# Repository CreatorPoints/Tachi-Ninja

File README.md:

# Tachi Ninja V2
A 60% Silent Linear mechanical keyboard that has per key RGB lighting and a display for pure asthetics! Made so that I can advance more in this fun cad pathway! [Now Hot-Swappable!]

---

## What was fun to make and what wasnt:
Well, it was overall a great project, I liked the most is the designing the pcb and making the case of this keyboard. But the ABSOLUTE brutal part was manually tracing all 424 pads :skull:

---

## Why did I make this?
I made it because I wanted a actually good keyboard, so instead of buying from online I decided to make my own. Advantages are I get to control how it would be and ofcource the flex :cool:

---

## Whats this "V2" Thingy?
So, when this project was submitted for forge, the reviewer returned the project for multiple reasons, one of it being incomplete PCBA, so, I improvised with something much better. The table would be the best:
|V1|V2|
|--|--|
|Permanent MX Switches|Kailh MX Hot Swappable sockets|
|Very crampy keycaps|Follows universal 19.05mm rule for keyboards|
|More compact, less polished|Kinda less compact, more polished|

## Need this? Here!
So, you need this same keyboard? NO PROBLEM! Its open-source!
1) Download this repo [assuming you know how to... just run git clone in your terminal]
2) Order the PCB - Preferebly from [JLCPCB](jlcpcb.com)
3) Gather the rest of the parts. Check [BOM](./BOM.md) 
4) Case files are in /CAD. Its upto you how to print [#Printing-Legion on slack].
5) Once your assembled PCB arrives, hand-solder the hot-swap sockets and OLED into the board (these are excluded from PCBA since they're through-hole/socketed). Press-fit switches into the hot-swap sockets and mount the PCB into the case and snap on keycaps.
6) Flash the firmware, hold both the BOOT and NRST button when turning on, it turns the stm32 to bootloader mode, drop the .h and json files on a STM32CubeProgrammer and Follow the steps there and then you are good to go!
7) Plug in via USB-C, confirm all 61 keys register, RGB lights up per-key, and the OLED display turns on! Yippe!

---

## Components used:
The following stuffs were used... Very hacky :)
- STM32F072C8Tx
- 1N4148 (x61)
- Kailh MX Hot Swappable Sockets (x61)
- SK6812MINI-E (x63)
- Resistors (x3)
- Capacitors (x6)
- Smol Switches (x2) - For boot & NRST purposes
- USB C 2.0 Receptable 16P
- AMS1117-3.3V
- 0.91 Inch I2C OLED Screen
- USBLC6-2SC6

---
## BOM

| Item | Link | Price | Shipping Cost |
| --- | --- | --- | --- |
| Switches (70x) | [HMX Taro Silent Linear](https://stackskb.com/store/hmx-taro-silent-linear-switch-pack-of-10/) | ₹2,625.00 / $27.39 | Free |
| Stabilizers | [Durock V2 Screw-in Stabilizers](https://stackskb.com/store/durock-clear-screw-in-stabilizers-v2/?attribute_combination=4%2B1+Set&attribute_spacebar-size=6.25U) | ₹1,595.00 / $16.65 | Free |
| Keycaps | [dagaladoo Shine Through Keycaps](https://www.amazon.in/gp/product/B0DJH6L159/ref=ox_sc_act_title_1?smid=A2BWJVKSWP7TR2) | ₹2,500.00 / $26.12 | $5.00 |
| Hot Swap Sockets (70x) | [Gateron Sockets](https://stackskb.com/store/gateron-hotswap-sockets/) | ₹610.00 / $6.37 | Free |
| Solder Wire | [Lead-free Solder](https://www.amazon.in/SCHOFIC-Solder-Sn99-Ag0-3-Cu0-7-Weight-0-22lb/dp/B078C7SMKY/ref=sr_1_10?sr=8-10) | ₹385.00 / $4.02 | Free |
| PCB & Top Assembly (2 boards) | [JLCPCB](https://jlcpcb.com) | $53.21 | Included |
| Loose SMD Parts (LEDs, Diodes, CC Resistors) | [LCSC](https://www.lcsc.com) | $9.03 *(parts + handling)* | $42.03 |

Subtotal: $189.82  
Estimated Import Customs (20% – 45% on JLCPCB + LCSC):** ~$21.00 – $47.00 (~$36.50 mid)  
Total Estimated Request: ~$226.30

### For the full itemized breakdown, footprints, and part numbers, check:
[BOM.md](BOM.md)

---

## Images!

### Wait, its V1

### From here V2 Development begins

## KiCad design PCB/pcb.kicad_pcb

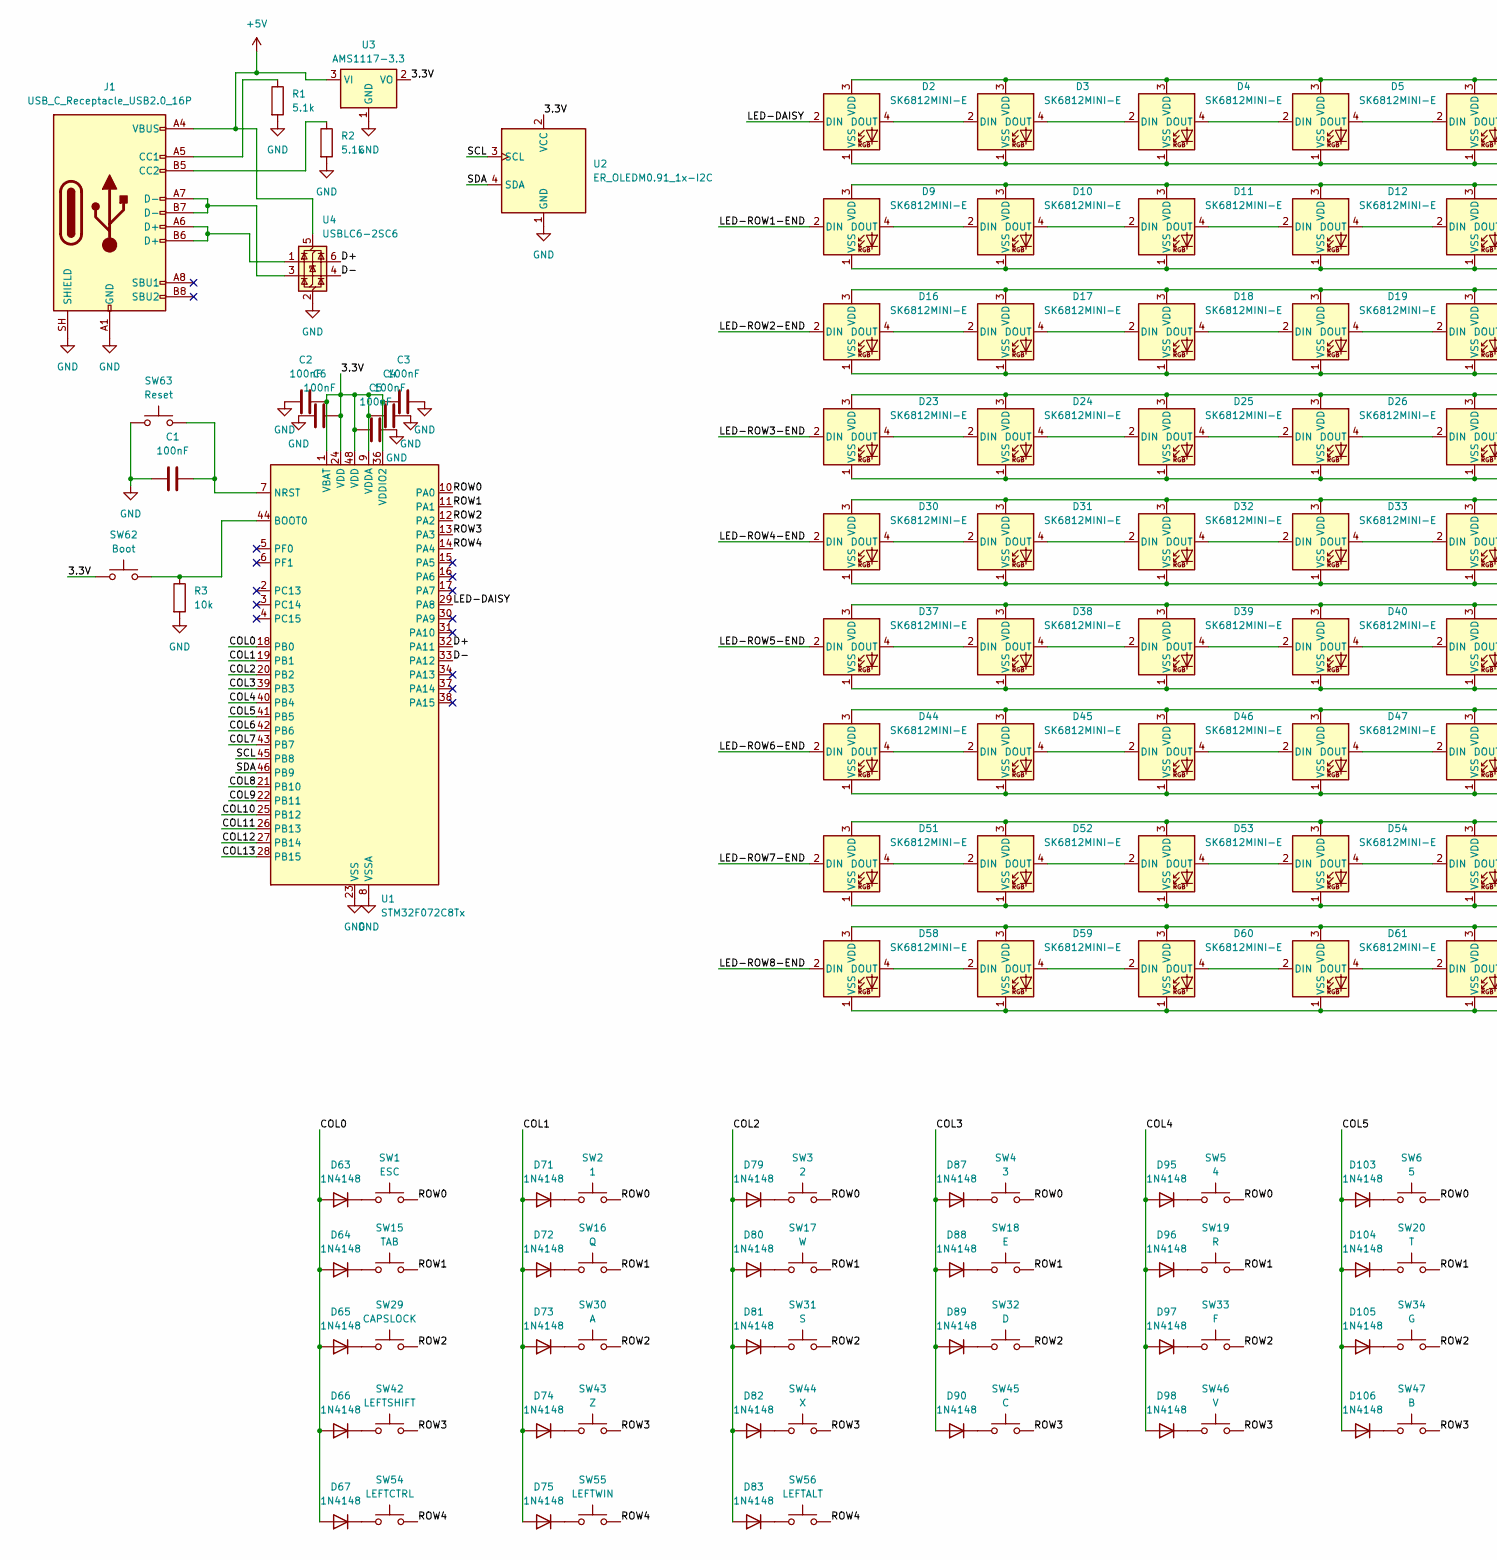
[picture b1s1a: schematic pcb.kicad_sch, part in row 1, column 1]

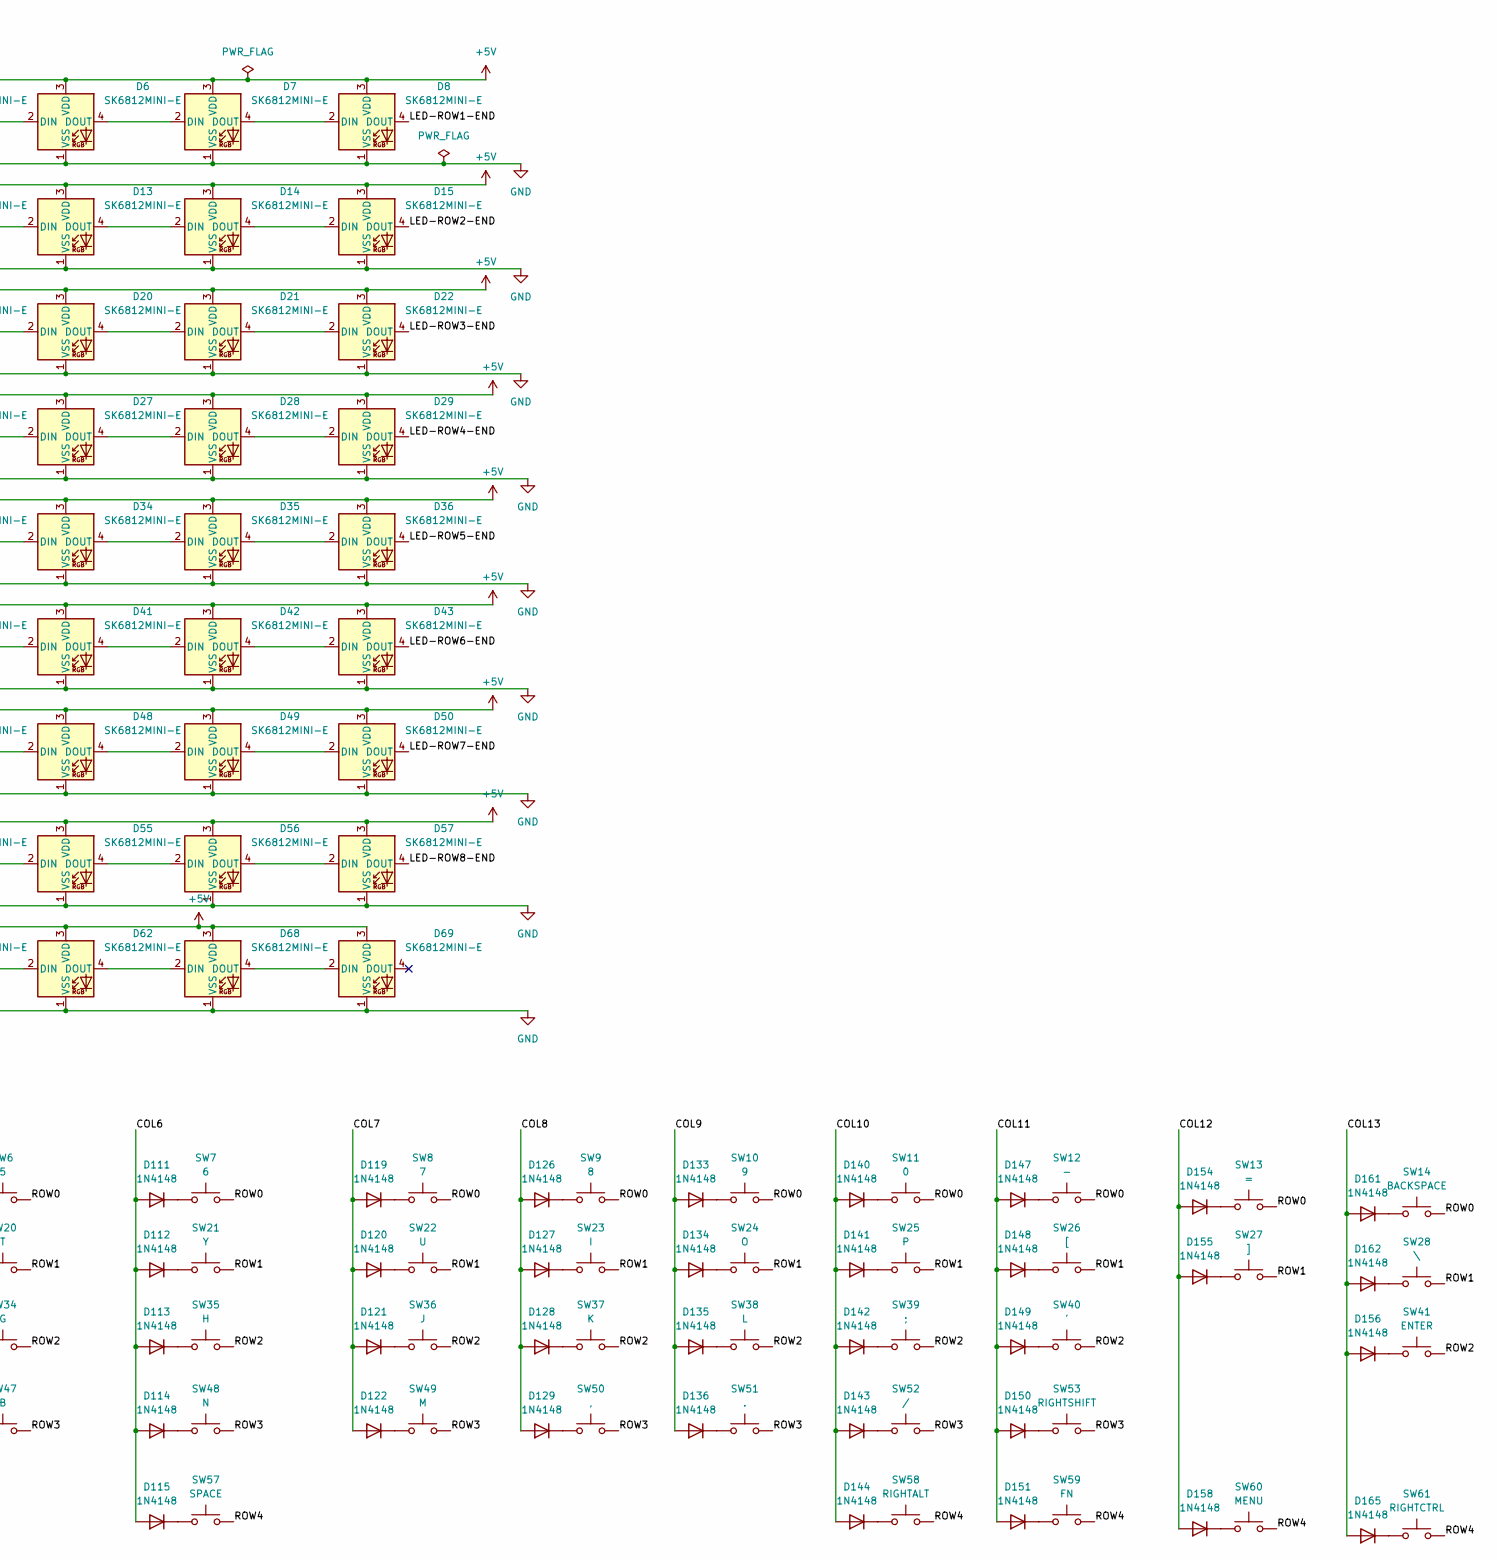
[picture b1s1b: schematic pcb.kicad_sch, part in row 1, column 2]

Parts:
C1, C2, C3, C4, C5, C6: 100nF; C_0805_2012Metric
D2, D3, D4, D5, D6, D7, D8, D9, D10, D11, D12, D13, D14, D15, D16, D17, D18, D19, D20, D21, D22, D23, D24, D25, D26, D27, D28, D29, D30, D31, D32, D33, D34, D35, D36, D37, D38, D39, D40, D41, D42, D43, D44, D45, D46, D47, D48, D49, D50, D51, D52, D53, D54, D55, D56, D57, D58, D59, D60, D61, D62, D68, D69: SK6812MINI-E; LED_SK6812MINI-E_3.2x2.8mm_P1.5mm_ReverseMount
D63, D64, D65, D66, D67, D71, D72, D73, D74, D75, D79, D80, D81, D82, D83, D87, D88, D89, D90, D95, D96, D97, D98, D103, D104, D105, D106, D111, D112, D113, D114, D115, D119, D120, D121, D122, D126, D127, D128, D129, D133, D134, D135, D136, D140, D141, D142, D143, D144, D147, D148, D149, D150, D151, D154, D155, D156, D158, D161, D162, D165: 1N4148; D_DO-35_SOD27_P7.62mm_Horizontal
J1: USB_C_Receptacle_USB2.0_16P; USB_C_Receptacle_HCTL_HC-TYPE-C-16P-01A
R1, R2: 5.1k; R_0603_1608Metric
R3: 10k; R_0603_1608Metric
SW1: ESC; SW_Hotswap_Kailh_MX_1.00u
SW2: 1; SW_Hotswap_Kailh_MX_1.00u
SW3: 2; SW_Hotswap_Kailh_MX_1.00u
SW4: 3; SW_Hotswap_Kailh_MX_1.00u
SW5: 4; SW_Hotswap_Kailh_MX_1.00u
SW6: 5; SW_Hotswap_Kailh_MX_1.00u
SW7: 6; SW_Hotswap_Kailh_MX_1.00u
SW8: 7; SW_Hotswap_Kailh_MX_1.00u
SW9: 8; SW_Hotswap_Kailh_MX_1.00u
SW10: 9; SW_Hotswap_Kailh_MX_1.00u
SW11: 0; SW_Hotswap_Kailh_MX_1.00u
SW12: -; SW_Hotswap_Kailh_MX_1.00u
SW13: =; SW_Hotswap_Kailh_MX_1.00u
SW14: BACKSPACE; SW_Hotswap_Kailh_MX_2.00u
SW15: TAB; SW_Hotswap_Kailh_MX_1.50u
SW16: Q; SW_Hotswap_Kailh_MX_1.00u
SW17: W; SW_Hotswap_Kailh_MX_1.00u
SW18: E; SW_Hotswap_Kailh_MX_1.00u
SW19: R; SW_Hotswap_Kailh_MX_1.00u
SW20: T; SW_Hotswap_Kailh_MX_1.00u
SW21: Y; SW_Hotswap_Kailh_MX_1.00u
SW22: U; SW_Hotswap_Kailh_MX_1.00u
SW23: I; SW_Hotswap_Kailh_MX_1.00u
SW24: O; SW_Hotswap_Kailh_MX_1.00u
SW25: P; SW_Hotswap_Kailh_MX_1.00u
SW26: [; SW_Hotswap_Kailh_MX_1.00u
SW27: ]; SW_Hotswap_Kailh_MX_1.00u
SW28: \; SW_Hotswap_Kailh_MX_1.50u
SW29: CAPSLOCK; SW_Hotswap_Kailh_MX_1.75u
SW30: A; SW_Hotswap_Kailh_MX_1.00u
SW31: S; SW_Hotswap_Kailh_MX_1.00u
SW32: D; SW_Hotswap_Kailh_MX_1.00u
SW33: F; SW_Hotswap_Kailh_MX_1.00u
SW34: G; SW_Hotswap_Kailh_MX_1.00u
SW35: H; SW_Hotswap_Kailh_MX_1.00u
SW36: J; SW_Hotswap_Kailh_MX_1.00u
SW37: K; SW_Hotswap_Kailh_MX_1.00u
SW38: L; SW_Hotswap_Kailh_MX_1.00u
SW39: ;; SW_Hotswap_Kailh_MX_1.00u
SW40: '; SW_Hotswap_Kailh_MX_1.00u
SW41: ENTER; SW_Hotswap_Kailh_MX_2.25u
SW42: LEFTSHIFT; SW_Hotswap_Kailh_MX_2.25u
SW43: Z; SW_Hotswap_Kailh_MX_1.00u
SW44: X; SW_Hotswap_Kailh_MX_1.00u
SW45: C; SW_Hotswap_Kailh_MX_1.00u
SW46: V; SW_Hotswap_Kailh_MX_1.00u
SW47: B; SW_Hotswap_Kailh_MX_1.00u
SW48: N; SW_Hotswap_Kailh_MX_1.00u
SW49: M; SW_Hotswap_Kailh_MX_1.00u
SW50: ,; SW_Hotswap_Kailh_MX_1.00u
SW51: .; SW_Hotswap_Kailh_MX_1.00u
SW52: /; SW_Hotswap_Kailh_MX_1.00u
SW53: RIGHTSHIFT; SW_Hotswap_Kailh_MX_2.75u
SW54: LEFTCTRL; SW_Hotswap_Kailh_MX_1.25u
SW55: LEFTWIN; SW_Hotswap_Kailh_MX_1.25u
SW56: LEFTALT; SW_Hotswap_Kailh_MX_1.25u
SW57: SPACE; SW_Hotswap_Kailh_MX_6.25u
SW58: RIGHTALT; SW_Hotswap_Kailh_MX_1.25u
SW59: FN; SW_Hotswap_Kailh_MX_1.25u
SW60: MENU; SW_Hotswap_Kailh_MX_1.25u
SW61: RIGHTCTRL; SW_Hotswap_Kailh_MX_1.25u
SW62: Boot; SW_SPST_B3U-1000P
SW63: Reset; SW_SPST_B3U-1000P
U1: STM32F072C8Tx; LQFP-48_7x7mm_P0.5mm
U2: ER_OLEDM0.91_1x-I2C
U3: AMS1117-3.3; SOT-223-3_TabPin2
U4: USBLC6-2SC6; SOT-23-6

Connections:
+5V: D2.3 (VDD), D3.3 (VDD), D4.3 (VDD), D5.3 (VDD), D6.3 (VDD), D7.3 (VDD), D8.3 (VDD), D9.3 (VDD), D10.3 (VDD), D11.3 (VDD), D12.3 (VDD), D13.3 (VDD), D14.3 (VDD), D15.3 (VDD), D16.3 (VDD), D17.3 (VDD), D18.3 (VDD), D19.3 (VDD), D20.3 (VDD), D21.3 (VDD), D22.3 (VDD), D23.3 (VDD), D24.3 (VDD), D25.3 (VDD), D26.3 (VDD), D27.3 (VDD), D28.3 (VDD), D29.3 (VDD), D30.3 (VDD), D31.3 (VDD), D32.3 (VDD), D33.3 (VDD), D34.3 (VDD), D35.3 (VDD), D36.3 (VDD), D37.3 (VDD), D38.3 (VDD), D39.3 (VDD), D40.3 (VDD), D41.3 (VDD), D42.3 (VDD), D43.3 (VDD), D44.3 (VDD), D45.3 (VDD), D46.3 (VDD), D47.3 (VDD), D48.3 (VDD), D49.3 (VDD), D50.3 (VDD), D51.3 (VDD), D52.3 (VDD), D53.3 (VDD), D54.3 (VDD), D55.3 (VDD), D56.3 (VDD), D57.3 (VDD), D58.3 (VDD), D59.3 (VDD), D60.3 (VDD), D61.3 (VDD), D62.3 (VDD), D68.3 (VDD), D69.3 (VDD), J1.A4 (VBUS), J1.A9 (VBUS), J1.B4 (VBUS), J1.B9 (VBUS), U3.3 (VI), U4.5 (VBUS)
/3.3V: C2.1, C3.2, C4.2, C5.2, C6.1, SW62.1, U1.1 (VBAT), U1.9 (VDDA), U1.24 (VDD), U1.36 (VDDIO2), U1.48 (VDD), U2.2 (VCC), U3.2 (VO)
/COL0: D63.2 (A), D64.2 (A), D65.2 (A), D66.2 (A), D67.2 (A), U1.18 (PB0)
/COL1: D71.2 (A), D72.2 (A), D73.2 (A), D74.2 (A), D75.2 (A), U1.19 (PB1)
/COL2: D79.2 (A), D80.2 (A), D81.2 (A), D82.2 (A), D83.2 (A), U1.20 (PB2)
/COL3: D87.2 (A), D88.2 (A), D89.2 (A), D90.2 (A), U1.39 (PB3)
/COL4: D95.2 (A), D96.2 (A), D97.2 (A), D98.2 (A), U1.40 (PB4)
/COL5: D103.2 (A), D104.2 (A), D105.2 (A), D106.2 (A), U1.41 (PB5)
/COL6: D111.2 (A), D112.2 (A), D113.2 (A), D114.2 (A), D115.2 (A), U1.42 (PB6)
/COL7: D119.2 (A), D120.2 (A), D121.2 (A), D122.2 (A), U1.43 (PB7)
/COL8: D126.2 (A), D127.2 (A), D128.2 (A), D129.2 (A), U1.21 (PB10)
/COL9: D133.2 (A), D134.2 (A), D135.2 (A), D136.2 (A), U1.22 (PB11)
/COL10: D140.2 (A), D141.2 (A), D142.2 (A), D143.2 (A), D144.2 (A), U1.25 (PB12)
/COL11: D147.2 (A), D148.2 (A), D149.2 (A), D150.2 (A), D151.2 (A), U1.26 (PB13)
/COL12: D154.2 (A), D155.2 (A), D158.2 (A), U1.27 (PB14)
/COL13: D156.2 (A), D161.2 (A), D162.2 (A), D165.2 (A), U1.28 (PB15)
/D+: U1.32 (PA11), U4.6 (I/O1)
/D-: U1.33 (PA12), U4.4 (I/O2)
/LED-DAISY: D2.2 (DIN), U1.29 (PA8)
/LED-ROW1-END: D8.4 (DOUT), D9.2 (DIN)
/LED-ROW2-END: D15.4 (DOUT), D16.2 (DIN)
/LED-ROW3-END: D22.4 (DOUT), D23.2 (DIN)
/LED-ROW4-END: D29.4 (DOUT), D30.2 (DIN)
/LED-ROW5-END: D36.4 (DOUT), D37.2 (DIN)
/LED-ROW6-END: D43.4 (DOUT), D44.2 (DIN)
/LED-ROW7-END: D50.4 (DOUT), D51.2 (DIN)
/LED-ROW8-END: D57.4 (DOUT), D58.2 (DIN)
/ROW0: SW1.2, SW2.2, SW3.2, SW4.2, SW5.2, SW6.2, SW7.2, SW8.2, SW9.2, SW10.2, SW11.2, SW12.2, SW13.2, SW14.2, U1.10 (PA0)
/ROW1: SW15.2, SW16.2, SW17.2, SW18.2, SW19.2, SW20.2, SW21.2, SW22.2, SW23.2, SW24.2, SW25.2, SW26.2, SW27.2, SW28.2, U1.11 (PA1)
/ROW2: SW29.2, SW30.2, SW31.2, SW32.2, SW33.2, SW34.2, SW35.2, SW36.2, SW37.2, SW38.2, SW39.2, SW40.2, SW41.2, U1.12 (PA2)
/ROW3: SW42.2, SW43.2, SW44.2, SW45.2, SW46.2, SW47.2, SW48.2, SW49.2, SW50.2, SW51.2, SW52.2, SW53.2, U1.13 (PA3)
/ROW4: SW54.2, SW55.2, SW56.2, SW57.2, SW58.2, SW59.2, SW60.2, SW61.2, U1.14 (PA4)
/SCL: U1.45 (PB8), U2.3 (SCL)
/SDA: U1.46 (PB9), U2.4 (SDA)
GND: C1.1, C2.2, C3.1, C4.1, C5.1, C6.2, D2.1 (VSS), D3.1 (VSS), D4.1 (VSS), D5.1 (VSS), D6.1 (VSS), D7.1 (VSS), D8.1 (VSS), D9.1 (VSS), D10.1 (VSS), D11.1 (VSS), D12.1 (VSS), D13.1 (VSS), D14.1 (VSS), D15.1 (VSS), D16.1 (VSS), D17.1 (VSS), D18.1 (VSS), D19.1 (VSS), D20.1 (VSS), D21.1 (VSS), D22.1 (VSS), D23.1 (VSS), D24.1 (VSS), D25.1 (VSS), D26.1 (VSS), D27.1 (VSS), D28.1 (VSS), D29.1 (VSS), D30.1 (VSS), D31.1 (VSS), D32.1 (VSS), D33.1 (VSS), D34.1 (VSS), D35.1 (VSS), D36.1 (VSS), D37.1 (VSS), D38.1 (VSS), D39.1 (VSS), D40.1 (VSS), D41.1 (VSS), D42.1 (VSS), D43.1 (VSS), D44.1 (VSS), D45.1 (VSS), D46.1 (VSS), D47.1 (VSS), D48.1 (VSS), D49.1 (VSS), D50.1 (VSS), D51.1 (VSS), D52.1 (VSS), D53.1 (VSS), D54.1 (VSS), D55.1 (VSS), D56.1 (VSS), D57.1 (VSS), D58.1 (VSS), D59.1 (VSS), D60.1 (VSS), D61.1 (VSS), D62.1 (VSS), D68.1 (VSS), D69.1 (VSS), J1.A1 (GND), J1.A12 (GND), J1.B1 (GND), J1.B12 (GND), J1.SH (SHIELD), R1.2, R2.2, R3.2, SW63.1, U1.8 (VSSA), U1.23 (VSS), U1.35 (VSS), U1.47 (VSS), U2.1 (GND), U3.1 (GND), U4.2 (GND)
unnamed: D2.4 (DOUT), D3.2 (DIN)
unnamed: D3.4 (DOUT), D4.2 (DIN)
unnamed: D4.4 (DOUT), D5.2 (DIN)
unnamed: D5.4 (DOUT), D6.2 (DIN)
unnamed: D6.4 (DOUT), D7.2 (DIN)
unnamed: D7.4 (DOUT), D8.2 (DIN)
unnamed: D9.4 (DOUT), D10.2 (DIN)
unnamed: D10.4 (DOUT), D11.2 (DIN)
unnamed: D11.4 (DOUT), D12.2 (DIN)
unnamed: D12.4 (DOUT), D13.2 (DIN)
unnamed: D13.4 (DOUT), D14.2 (DIN)
unnamed: D14.4 (DOUT), D15.2 (DIN)
unnamed: D16.4 (DOUT), D17.2 (DIN)
unnamed: D17.4 (DOUT), D18.2 (DIN)
unnamed: D18.4 (DOUT), D19.2 (DIN)
unnamed: D19.4 (DOUT), D20.2 (DIN)
unnamed: D20.4 (DOUT), D21.2 (DIN)
unnamed: D21.4 (DOUT), D22.2 (DIN)
unnamed: D23.4 (DOUT), D24.2 (DIN)
unnamed: D24.4 (DOUT), D25.2 (DIN)
unnamed: D25.4 (DOUT), D26.2 (DIN)
unnamed: D26.4 (DOUT), D27.2 (DIN)
unnamed: D27.4 (DOUT), D28.2 (DIN)
unnamed: D28.4 (DOUT), D29.2 (DIN)
unnamed: D30.4 (DOUT), D31.2 (DIN)
unnamed: D31.4 (DOUT), D32.2 (DIN)
unnamed: D32.4 (DOUT), D33.2 (DIN)
unnamed: D33.4 (DOUT), D34.2 (DIN)
unnamed: D34.4 (DOUT), D35.2 (DIN)
unnamed: D35.4 (DOUT), D36.2 (DIN)
unnamed: D37.4 (DOUT), D38.2 (DIN)
unnamed: D38.4 (DOUT), D39.2 (DIN)
unnamed: D39.4 (DOUT), D40.2 (DIN)
unnamed: D40.4 (DOUT), D41.2 (DIN)
unnamed: D41.4 (DOUT), D42.2 (DIN)
unnamed: D42.4 (DOUT), D43.2 (DIN)
unnamed: D44.4 (DOUT), D45.2 (DIN)
unnamed: D45.4 (DOUT), D46.2 (DIN)
unnamed: D46.4 (DOUT), D47.2 (DIN)
unnamed: D47.4 (DOUT), D48.2 (DIN)
unnamed: D48.4 (DOUT), D49.2 (DIN)
unnamed: D49.4 (DOUT), D50.2 (DIN)
unnamed: D51.4 (DOUT), D52.2 (DIN)
unnamed: D52.4 (DOUT), D53.2 (DIN)
unnamed: D53.4 (DOUT), D54.2 (DIN)
unnamed: D54.4 (DOUT), D55.2 (DIN)
unnamed: D55.4 (DOUT), D56.2 (DIN)
unnamed: D56.4 (DOUT), D57.2 (DIN)
unnamed: D58.4 (DOUT), D59.2 (DIN)
unnamed: D59.4 (DOUT), D60.2 (DIN)
unnamed: D60.4 (DOUT), D61.2 (DIN)
unnamed: D61.4 (DOUT), D62.2 (DIN)
unnamed: D62.4 (DOUT), D68.2 (DIN)
unnamed: D63.1 (K), SW1.1
unnamed: D64.1 (K), SW15.1
unnamed: D65.1 (K), SW29.1
unnamed: D66.1 (K), SW42.1
unnamed: D67.1 (K), SW54.1
unnamed: D68.4 (DOUT), D69.2 (DIN)
unnamed: D71.1 (K), SW2.1
unnamed: D72.1 (K), SW16.1
unnamed: D73.1 (K), SW30.1
unnamed: D74.1 (K), SW43.1
unnamed: D75.1 (K), SW55.1
unnamed: D79.1 (K), SW3.1
unnamed: D80.1 (K), SW17.1
unnamed: D81.1 (K), SW31.1
unnamed: D82.1 (K), SW44.1
unnamed: D83.1 (K), SW56.1
unnamed: D87.1 (K), SW4.1
unnamed: D88.1 (K), SW18.1
unnamed: D89.1 (K), SW32.1
unnamed: D90.1 (K), SW45.1
unnamed: D95.1 (K), SW5.1
unnamed: D96.1 (K), SW19.1
unnamed: D97.1 (K), SW33.1
unnamed: D98.1 (K), SW46.1
unnamed: D103.1 (K), SW6.1
unnamed: D104.1 (K), SW20.1
unnamed: D105.1 (K), SW34.1
unnamed: D106.1 (K), SW47.1
unnamed: D111.1 (K), SW7.1
unnamed: D112.1 (K), SW21.1
unnamed: D113.1 (K), SW35.1
unnamed: D114.1 (K), SW48.1
unnamed: D115.1 (K), SW57.1
unnamed: D119.1 (K), SW8.1
unnamed: D120.1 (K), SW22.1
unnamed: D121.1 (K), SW36.1
unnamed: D122.1 (K), SW49.1
unnamed: D126.1 (K), SW9.1
unnamed: D127.1 (K), SW23.1
unnamed: D128.1 (K), SW37.1
unnamed: D129.1 (K), SW50.1
unnamed: D133.1 (K), SW10.1
unnamed: D134.1 (K), SW24.1
unnamed: D135.1 (K), SW38.1
unnamed: D136.1 (K), SW51.1
unnamed: D140.1 (K), SW11.1
unnamed: D141.1 (K), SW25.1
unnamed: D142.1 (K), SW39.1
unnamed: D143.1 (K), SW52.1
unnamed: D144.1 (K), SW58.1
unnamed: D147.1 (K), SW12.1
unnamed: D148.1 (K), SW26.1
unnamed: D149.1 (K), SW40.1
unnamed: D150.1 (K), SW53.1
unnamed: D151.1 (K), SW59.1
unnamed: D154.1 (K), SW13.1
unnamed: D155.1 (K), SW27.1
unnamed: D156.1 (K), SW41.1
unnamed: D158.1 (K), SW60.1
unnamed: D161.1 (K), SW14.1
unnamed: D162.1 (K), SW28.1
unnamed: D165.1 (K), SW61.1
unnamed: J1.A5 (CC1), R1.1
unnamed: J1.B5 (CC2), R2.1
unnamed: J1.A6 (D+), J1.B6 (D+), U4.1 (I/O1)
unnamed: J1.A7 (D-), J1.B7 (D-), U4.3 (I/O2)
unnamed: R3.1, SW62.2, U1.44 (BOOT0)
unnamed: C1.2, SW63.2, U1.7 (NRST)

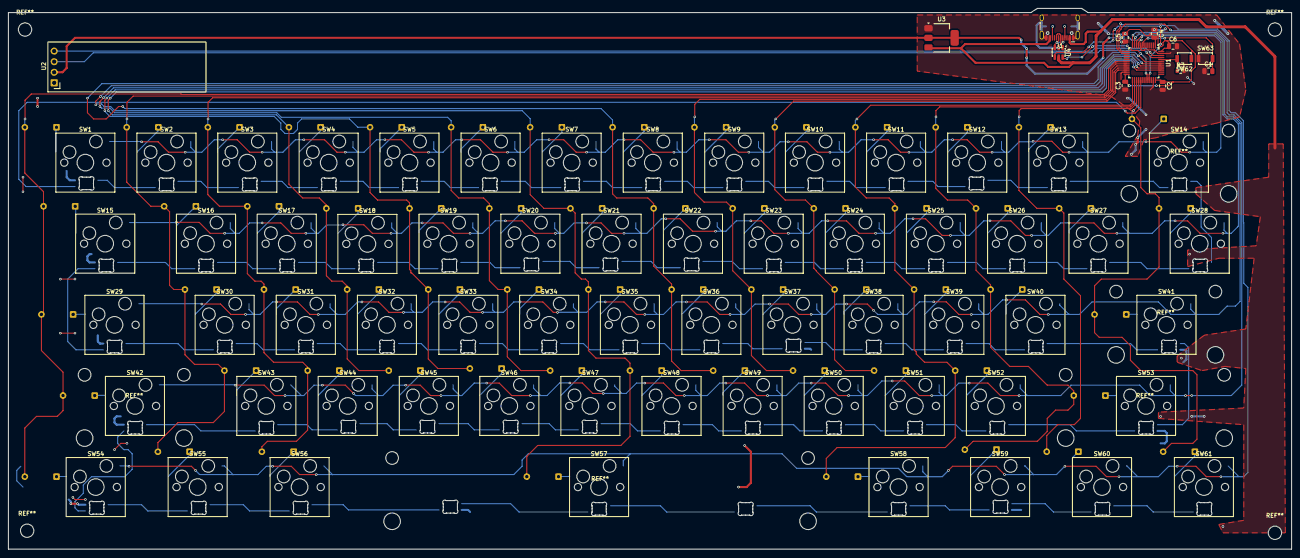
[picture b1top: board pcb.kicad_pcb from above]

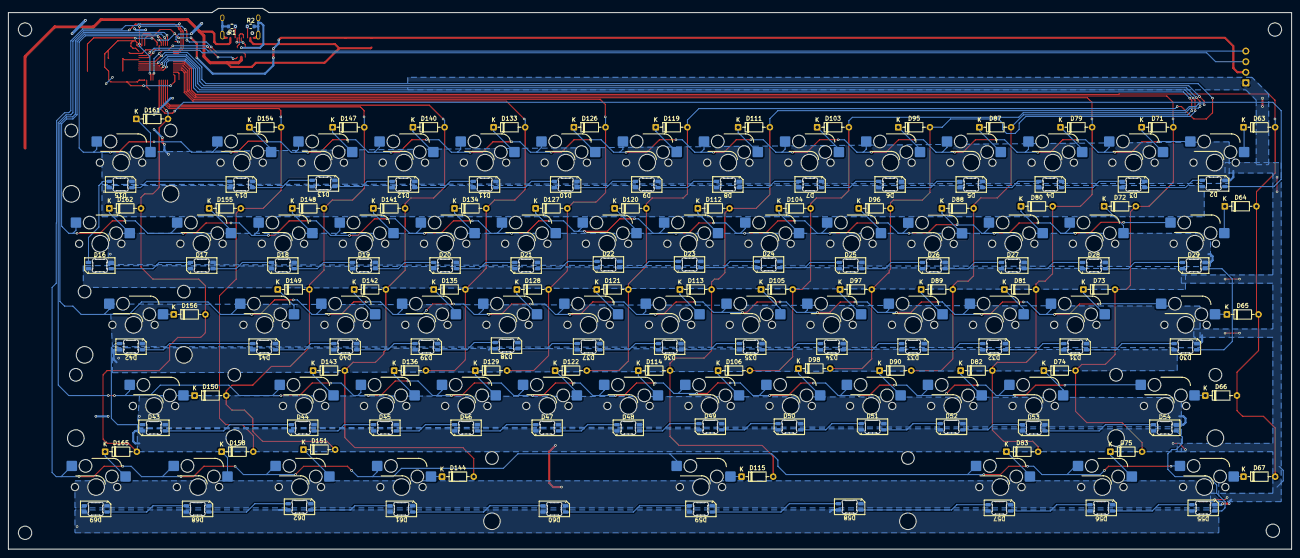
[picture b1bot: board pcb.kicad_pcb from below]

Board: 2 copper layers, 308.5 x 130.0 mm, 201 parts (126 on the bottom side), 156 nets.

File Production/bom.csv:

Designator,Footprint,Quantity,Value,LCSC Part #
BOOT,SW_SPST_B3U-1000P,1,Boot,
"C1, C2, C3, C4, C5, C6",0805,6,100nF,
"D10, D11, D12, D13, D14, D15, D16, D17, D18, D19, D2, D20, D21, D22, D23, D24, D25, D26, D27, D28, D29, D3, D30, D31, D32, D33, D34, D35, D36, D37, D38, D39, D4, D40, D41, D42, D43, D44, D45, D46, D47, D48, D49, D5, D50, D51, D52, D53, D54, D55, D56, D57, D58, D59, D6, D60, D61, D62, D68, D69, D7, D8, D9",LED_SK6812MINI-E_3.2x2.8mm_P1.5mm_ReverseMount,63,SK6812MINI-E,
"D103, D104, D105, D106, D111, D112, D113, D114, D115, D119, D120, D121, D122, D126, D127, D128, D129, D133, D134, D135, D136, D140, D141, D142, D143, D144, D147, D148, D149, D150, D151, D154, D155, D156, D158, D161, D162, D165, D63, D64, D65, D66, D67, D71, D72, D73, D74, D75, D79, D80, D81, D82, D83, D87, D88, D89, D90, D95, D96, D97, D98",D_DO-35_SOD27_P7.62mm_Horizontal,61,1N4148,
J1,USB_C_Receptacle_HCTL_HC-TYPE-C-16P-01A,1,USB_C_Receptacle_USB2.0_16P,
"R1, R2",0603,2,5.1k,
R3,0603,1,10k,
RESET,SW_SPST_B3U-1000P,1,Reset,
SW1,SW_Cherry_MX_1.50u_PCB,1,Tab,
SW10,SW_Cherry_MX_1.25u_PCB,1,Left_Ctrl,
SW11,SW_Cherry_MX_1.25u_PCB,1,Left_Win,
SW12,SW_Cherry_MX_1.25u_PCB,1,Left_Alt,
SW13,SW_Cherry_MX_1.25u_PCB,1,Fn,
SW14,SW_Cherry_MX_1.00u_PCB,1,Esc,
SW15,SW_Cherry_MX_1.00u_PCB,1,1,
SW16,SW_Cherry_MX_1.00u_PCB,1,2,
SW17,SW_Cherry_MX_1.00u_PCB,1,3,
SW18,SW_Cherry_MX_1.00u_PCB,1,4,
SW19,SW_Cherry_MX_1.00u_PCB,1,5,
SW2,SW_Cherry_MX_1.75u_PCB,1,Caps_Lock,
SW20,SW_Cherry_MX_1.00u_PCB,1,6,
SW21,SW_Cherry_MX_1.00u_PCB,1,7,
SW22,SW_Cherry_MX_1.00u_PCB,1,8,
SW23,SW_Cherry_MX_1.00u_PCB,1,9,
SW24,SW_Cherry_MX_1.00u_PCB,1,0,
SW25,SW_Cherry_MX_1.00u_PCB,1,-,
SW26,SW_Cherry_MX_1.00u_PCB,1,=,
SW27,SW_Cherry_MX_1.00u_PCB,1,Q,
SW28,SW_Cherry_MX_1.00u_PCB,1,W,
SW29,SW_Cherry_MX_1.00u_PCB,1,E,
SW3,SW_Cherry_MX_2.25u_PCB,1,Left_Shift,
SW30,SW_Cherry_MX_1.00u_PCB,1,R,
SW31,SW_Cherry_MX_1.00u_PCB,1,T,
SW32,SW_Cherry_MX_1.00u_PCB,1,Y,
SW33,SW_Cherry_MX_1.00u_PCB,1,U,
SW34,SW_Cherry_MX_1.00u_PCB,1,I,
SW35,SW_Cherry_MX_1.00u_PCB,1,O,
SW36,SW_Cherry_MX_1.00u_PCB,1,P,
SW37,SW_Cherry_MX_1.00u_PCB,1,[,
SW38,SW_Cherry_MX_1.00u_PCB,1,],
SW39,SW_Cherry_MX_1.50u_PCB,1,\,
SW4,SW_Cherry_MX_2.00u_PCB,1,Backspace,
SW40,SW_Cherry_MX_1.00u_PCB,1,A,
SW41,SW_Cherry_MX_1.00u_PCB,1,S,
SW42,SW_Cherry_MX_1.00u_PCB,1,D,
SW43,SW_Cherry_MX_1.00u_PCB,1,F,
SW44,SW_Cherry_MX_1.00u_PCB,1,G,
SW45,SW_Cherry_MX_1.00u_PCB,1,H,
SW46,SW_Cherry_MX_1.00u_PCB,1,J,
SW47,SW_Cherry_MX_1.00u_PCB,1,K,
SW48,SW_Cherry_MX_1.00u_PCB,1,L,
SW49,SW_Cherry_MX_1.00u_PCB,1,;,
SW5,SW_Cherry_MX_2.25u_PCB,1,Enter,
SW50,SW_Cherry_MX_1.00u_PCB,1,',
SW51,SW_Cherry_MX_1.00u_PCB,1,Z,
SW52,SW_Cherry_MX_1.00u_PCB,1,X,
SW53,SW_Cherry_MX_1.00u_PCB,1,C,
SW54,SW_Cherry_MX_1.00u_PCB,1,V,
SW55,SW_Cherry_MX_1.00u_PCB,1,B,
SW56,SW_Cherry_MX_1.00u_PCB,1,N,
SW57,SW_Cherry_MX_1.00u_PCB,1,M,
SW58,SW_Cherry_MX_1.00u_PCB,1,",",
SW59,SW_Cherry_MX_1.00u_PCB,1,.,
SW6,SW_Cherry_MX_2.75u_PCB,1,Right_Shift,
SW60,SW_Cherry_MX_1.00u_PCB,1,/,
SW61,SW_Cherry_MX_1.25u_PCB,1,MENU,
SW7,SW_Cherry_MX_6.25u_PCB,1,Spacebar,
SW8,SW_Cherry_MX_1.25u_PCB,1,Right_Ctrl,
SW9,SW_Cherry_MX_1.25u_PCB,1,Right_Alt,
U1,LQFP-48_7x7mm_P0.5mm,1,STM32F072C8Tx,
U2,ER_OLEDM0.91_1x-I2C,1,ER_OLEDM0.91_1x-I2C,
U3,SOT-223-3_TabPin2,1,AMS1117-3.3,
U4,SOT-23-6,1,USBLC6-2SC6,

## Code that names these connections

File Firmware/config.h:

#pragma once

/* ===== Matrix (verified against pcb.kicad_sch net labels) ===== */
#define MATRIX_ROW_PINS { A0, A1, A2, A3, A4 }
#define MATRIX_COL_PINS { B0, B1, B2, B3, B4, B5, B6, B7, B10, B11, B12, B13, B14, B15 }
#define DIODE_DIRECTION COL2ROW  // confirmed: D64 anode->COL0, cathode->switch->ROW1
#define DEBOUNCE 5

/* ===== RGB Matrix (WS2812 daisy chain, 64 LEDs) ===== */
#define RGB_MATRIX_LED_COUNT 64
#define RGB_DI_PIN A8           // confirmed: net "LED-DAISY" on PA8
#define WS2812_PWM_DRIVER PWMD1 // TODO: verify timer/channel — PA8 is TIM1_CH1 on F072, confirm in ChibiOS mcuconf.h
#define WS2812_PWM_CHANNEL 1
#define WS2812_DMA_STREAM STM32_DMA1_STREAM2
#define WS2812_DMA_CHANNEL 5

#define RGB_MATRIX_KEYPRESSES
#define RGB_MATRIX_DEFAULT_MODE RGB_MATRIX_CYCLE_LEFT_RIGHT
#define RGB_MATRIX_DEFAULT_HUE 0
#define RGB_MATRIX_DEFAULT_SAT 255
#define RGB_MATRIX_DEFAULT_VAL 120   // capped below max to keep current draw reasonable — raise carefully
#define RGB_MATRIX_DEFAULT_SPD 128
#define RGB_MATRIX_MAXIMUM_BRIGHTNESS 180 // safety cap given 64 LEDs on shared 5V rail

/* ===== I2C (OLED, if you enable OLED_ENABLE in rules.mk) ===== */
// Confirmed from schematic: SCL = PB8, SDA = PB9
#define I2C1_SCL_PIN B8
#define I2C1_SDA_PIN B9
#define I2C1_SCL_PAL_MODE 1   // TODO: verify AF mode number for I2C1 on F072 in ChibiOS docs
#define I2C1_SDA_PAL_MODE 1

/* ===== USB ===== */
#define USB_MAX_POWER_CONSUMPTION 500

/* ===== Debounce / NKRO ===== */
#define FORCE_NKRO
